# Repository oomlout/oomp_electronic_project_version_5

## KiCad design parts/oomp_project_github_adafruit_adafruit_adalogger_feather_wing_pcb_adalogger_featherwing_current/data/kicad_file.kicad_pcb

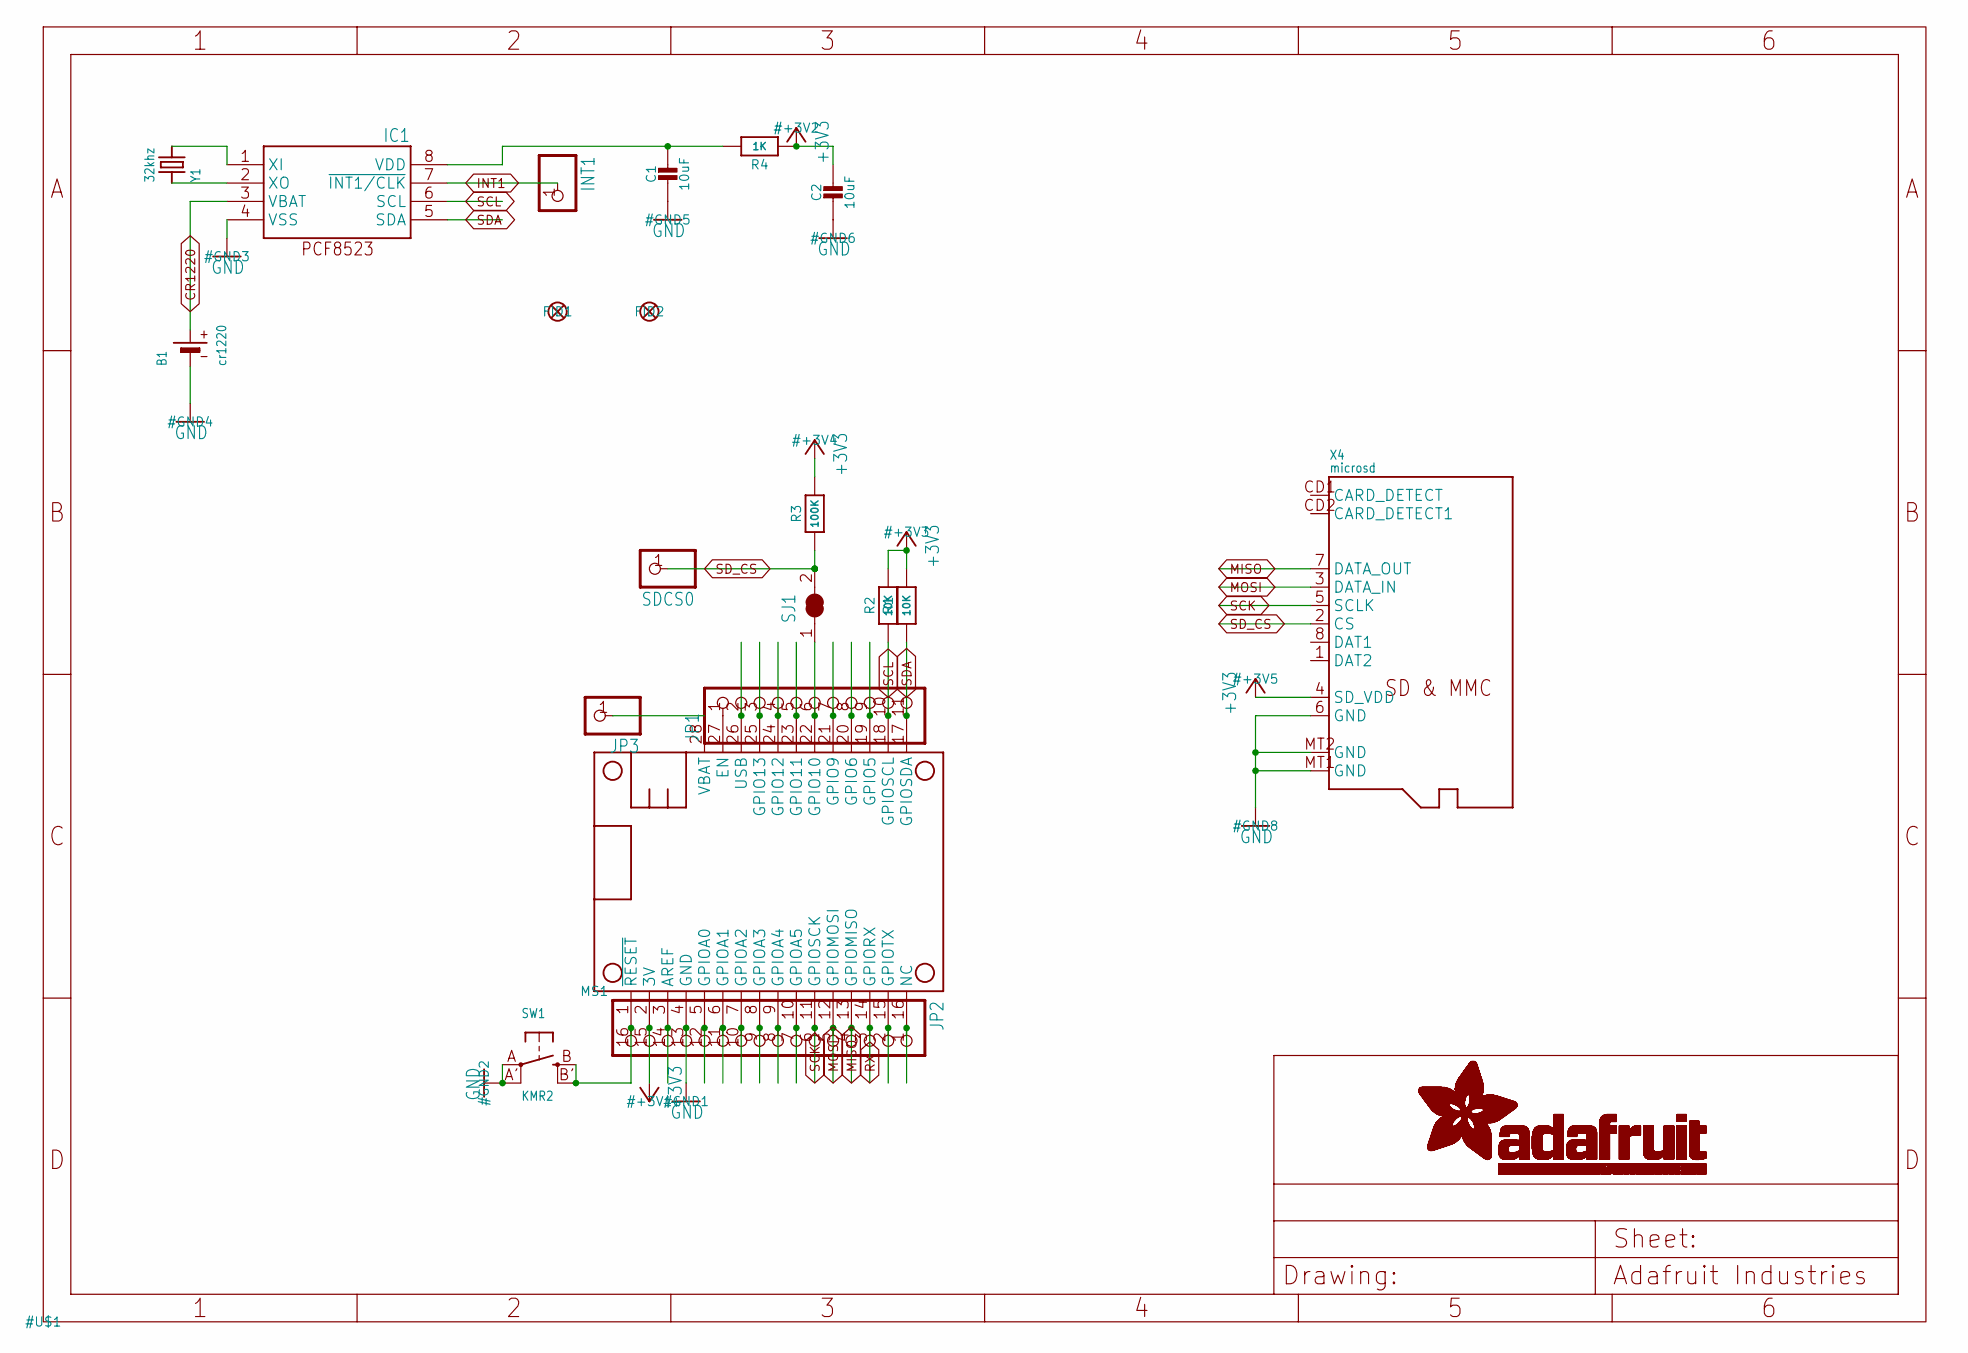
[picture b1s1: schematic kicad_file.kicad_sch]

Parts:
B1: cr1220; CR1220-2
C1, C2: 10uF; 0805-NO
FID1, FID2: FIDUCIAL_1MM
IC1: PCF8523T; SOIC8_150MIL
INT1: HEADER-1X1ROUND; 1X01_ROUND
JP1: HEADER-1X11; 1X11_ROUND
JP2: HEADER-1X16ROUND; 1X16_ROUND
JP3: HEADER-1X1ROUND; 1X01_ROUND
MS1: FEATHERWING_NODIM
R1, R2: 10K; 0603-NO
R3: 100K; 0603-NO
R4: 1K; 0603-NO
SDCS0: HEADER-1X1ROUND; 1X01_ROUND
SJ1: SOLDERJUMPER_CLOSED; SOLDERJUMPER_CLOSEDWIRE
SW1: KMR2; BTN_KMR2_4.6X2.8
X4: microsd; MICROSD
Y1: 32khz; CRYSTAL_8X3.8

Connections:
+3V3: C2.1, JP2.15, MS1.2 (3V), R1.2, R2.2, R3.2, R4.1, X4.4 (SD_VDD)
A: JP2.12, MS1.5 (GPIOA0)
AREF: JP2.14, MS1.3 (AREF)
B: JP2.11, MS1.6 (GPIOA1)
C: JP2.10, MS1.7 (GPIOA2)
CR1220: B1.+, IC1.3 (VBAT)
CS: JP1.6, MS1.22 (GPIO10), SJ1.1
D: JP2.9, MS1.8 (GPIOA3)
E: JP2.8, MS1.9 (GPIOA4)
EN: JP1.1, MS1.27 (EN)
F: JP2.7, MS1.10 (GPIOA5)
G: JP2.1, MS1.16 (NC)
GND: B1.-, C1.2, C2.2, IC1.4 (VSS), JP2.13, MS1.4 (GND), SW1.A, SW1.A' (P1), X4.6 (GND), X4.MT1 (GND), X4.MT2 (GND)
H: JP1.9, MS1.19 (GPIO5)
I: JP1.8, MS1.20 (GPIO6)
INT1: IC1.7 (~INT1/CLK), INT1.1
J: JP1.7, MS1.21 (GPIO9)
L: JP1.5, MS1.23 (GPIO11)
M: JP1.4, MS1.24 (GPIO12)
MISO: JP2.4, MS1.13 (GPIOMISO), X4.7 (DATA_OUT)
MOSI: JP2.5, MS1.12 (GPIOMOSI), X4.3 (DATA_IN)
N: JP1.3, MS1.25 (GPIO13)
unnamed: C1.1, IC1.8 (VDD), R4.2
unnamed: IC1.1 (XI), Y1.P$4 (2)
unnamed: IC1.2 (XO), Y1.P$1 (1)
RESET: JP2.16, MS1.1 (~RESET), SW1.B (S), SW1.B' (S1)
RX: JP2.3, MS1.14 (GPIORX)
SCK: JP2.6, MS1.11 (GPIOSCK), X4.5 (SCLK)
SCL: IC1.6 (SCL), JP1.10, MS1.18 (GPIOSCL), R2.1
SDA: IC1.5 (SDA), JP1.11, MS1.17 (GPIOSDA), R1.1
SD_CS: R3.1, SDCS0.1, SJ1.2, X4.2 (CS)
TX: JP2.2, MS1.15 (GPIOTX)
USB: JP1.2, MS1.26 (USB)
VBAT: JP3.1, MS1.28 (VBAT)

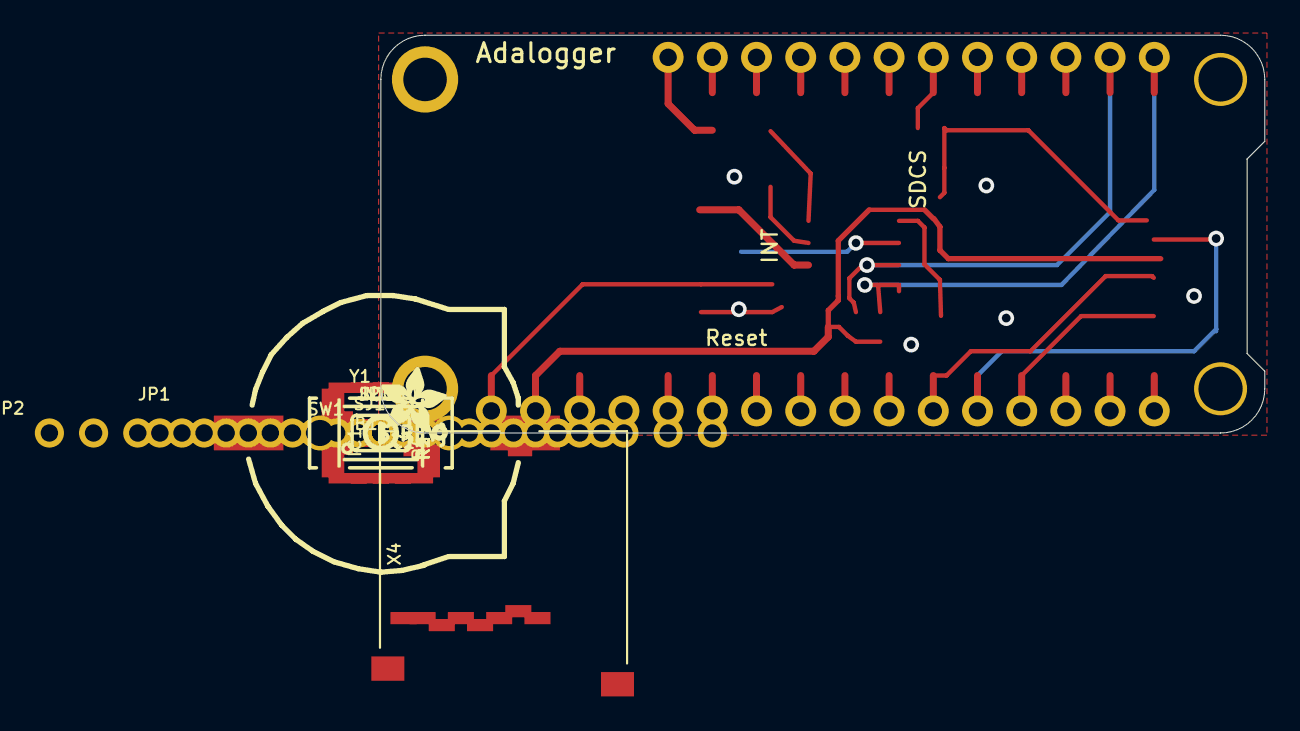
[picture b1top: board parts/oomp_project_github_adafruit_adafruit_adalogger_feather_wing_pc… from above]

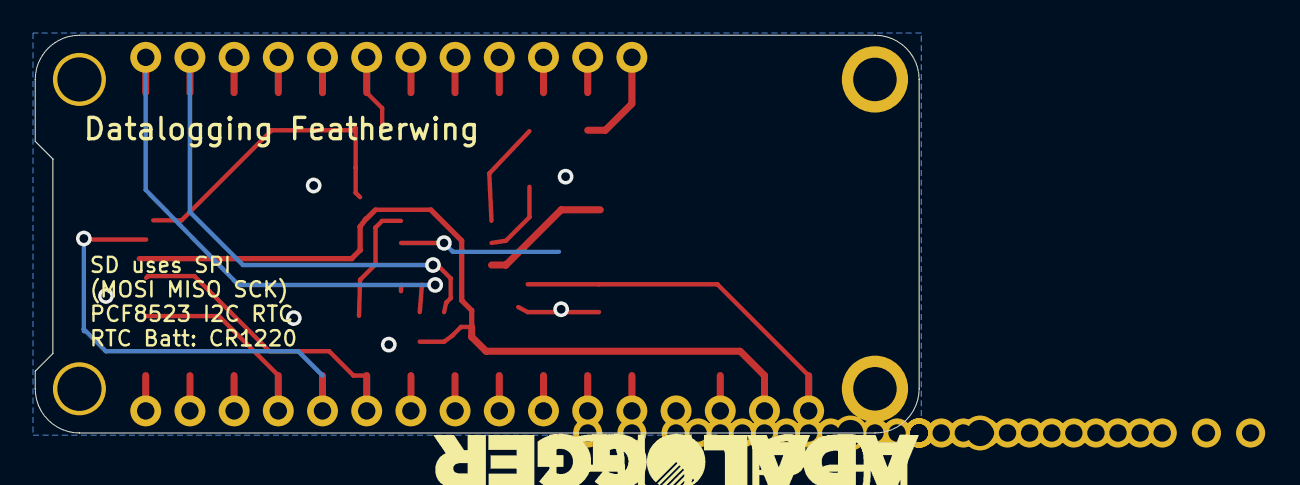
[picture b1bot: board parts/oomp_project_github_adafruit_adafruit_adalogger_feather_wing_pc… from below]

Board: 2 copper layers, 50.8 x 22.9 mm, 24 parts (2 on the bottom side), 34 nets.

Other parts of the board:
U$2: FEATHERLOGO
U$3: ADALOGGER_LOGO
U$4: ADAFRUIT_3.5MM
U$5: PCBFEAT-REV-040

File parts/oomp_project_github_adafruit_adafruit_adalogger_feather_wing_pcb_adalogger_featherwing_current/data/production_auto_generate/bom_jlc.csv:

Comment,Designator,Footprint,LCSC Part #
,"INT1,JP3,SDCS0",adalogger featherwing-import-fps:1X01_ROUND,C7501259
,JP1,adalogger featherwing-import-fps:1X11_ROUND,C2894934
,JP2,adalogger featherwing-import-fps:1X16_ROUND,C7501270
,U$4,adalogger featherwing-import-fps:ADAFRUIT_3.5MM,
,U$3,adalogger featherwing-import-fps:ADALOGGER_LOGO,
,U$2,adalogger featherwing-import-fps:FEATHERLOGO,
,U$5,adalogger featherwing-import-fps:PCBFEAT-REV-040,
100K,R3,adalogger featherwing-import-fps:0603-NO,C25803
10K,"R1,R2",adalogger featherwing-import-fps:0603-NO,C98220
10uF,"C1,C2",adalogger featherwing-import-fps:0805-NO,
1K,R4,adalogger featherwing-import-fps:0603-NO,C2907002
32khz,Y1,adalogger featherwing-import-fps:CRYSTAL_8X3.8,
cr1220,B1,adalogger featherwing-import-fps:CR1220-2,
FEATHERWING_NODIM,MS1,adalogger featherwing-import-fps:FEATHERWING_NODIM,
KMR2,SW1,adalogger featherwing-import-fps:BTN_KMR2_4.6X2.8,
microsd,X4,adalogger featherwing-import-fps:MICROSD,
PCF8523T,IC1,adalogger featherwing-import-fps:SOIC8_150MIL,

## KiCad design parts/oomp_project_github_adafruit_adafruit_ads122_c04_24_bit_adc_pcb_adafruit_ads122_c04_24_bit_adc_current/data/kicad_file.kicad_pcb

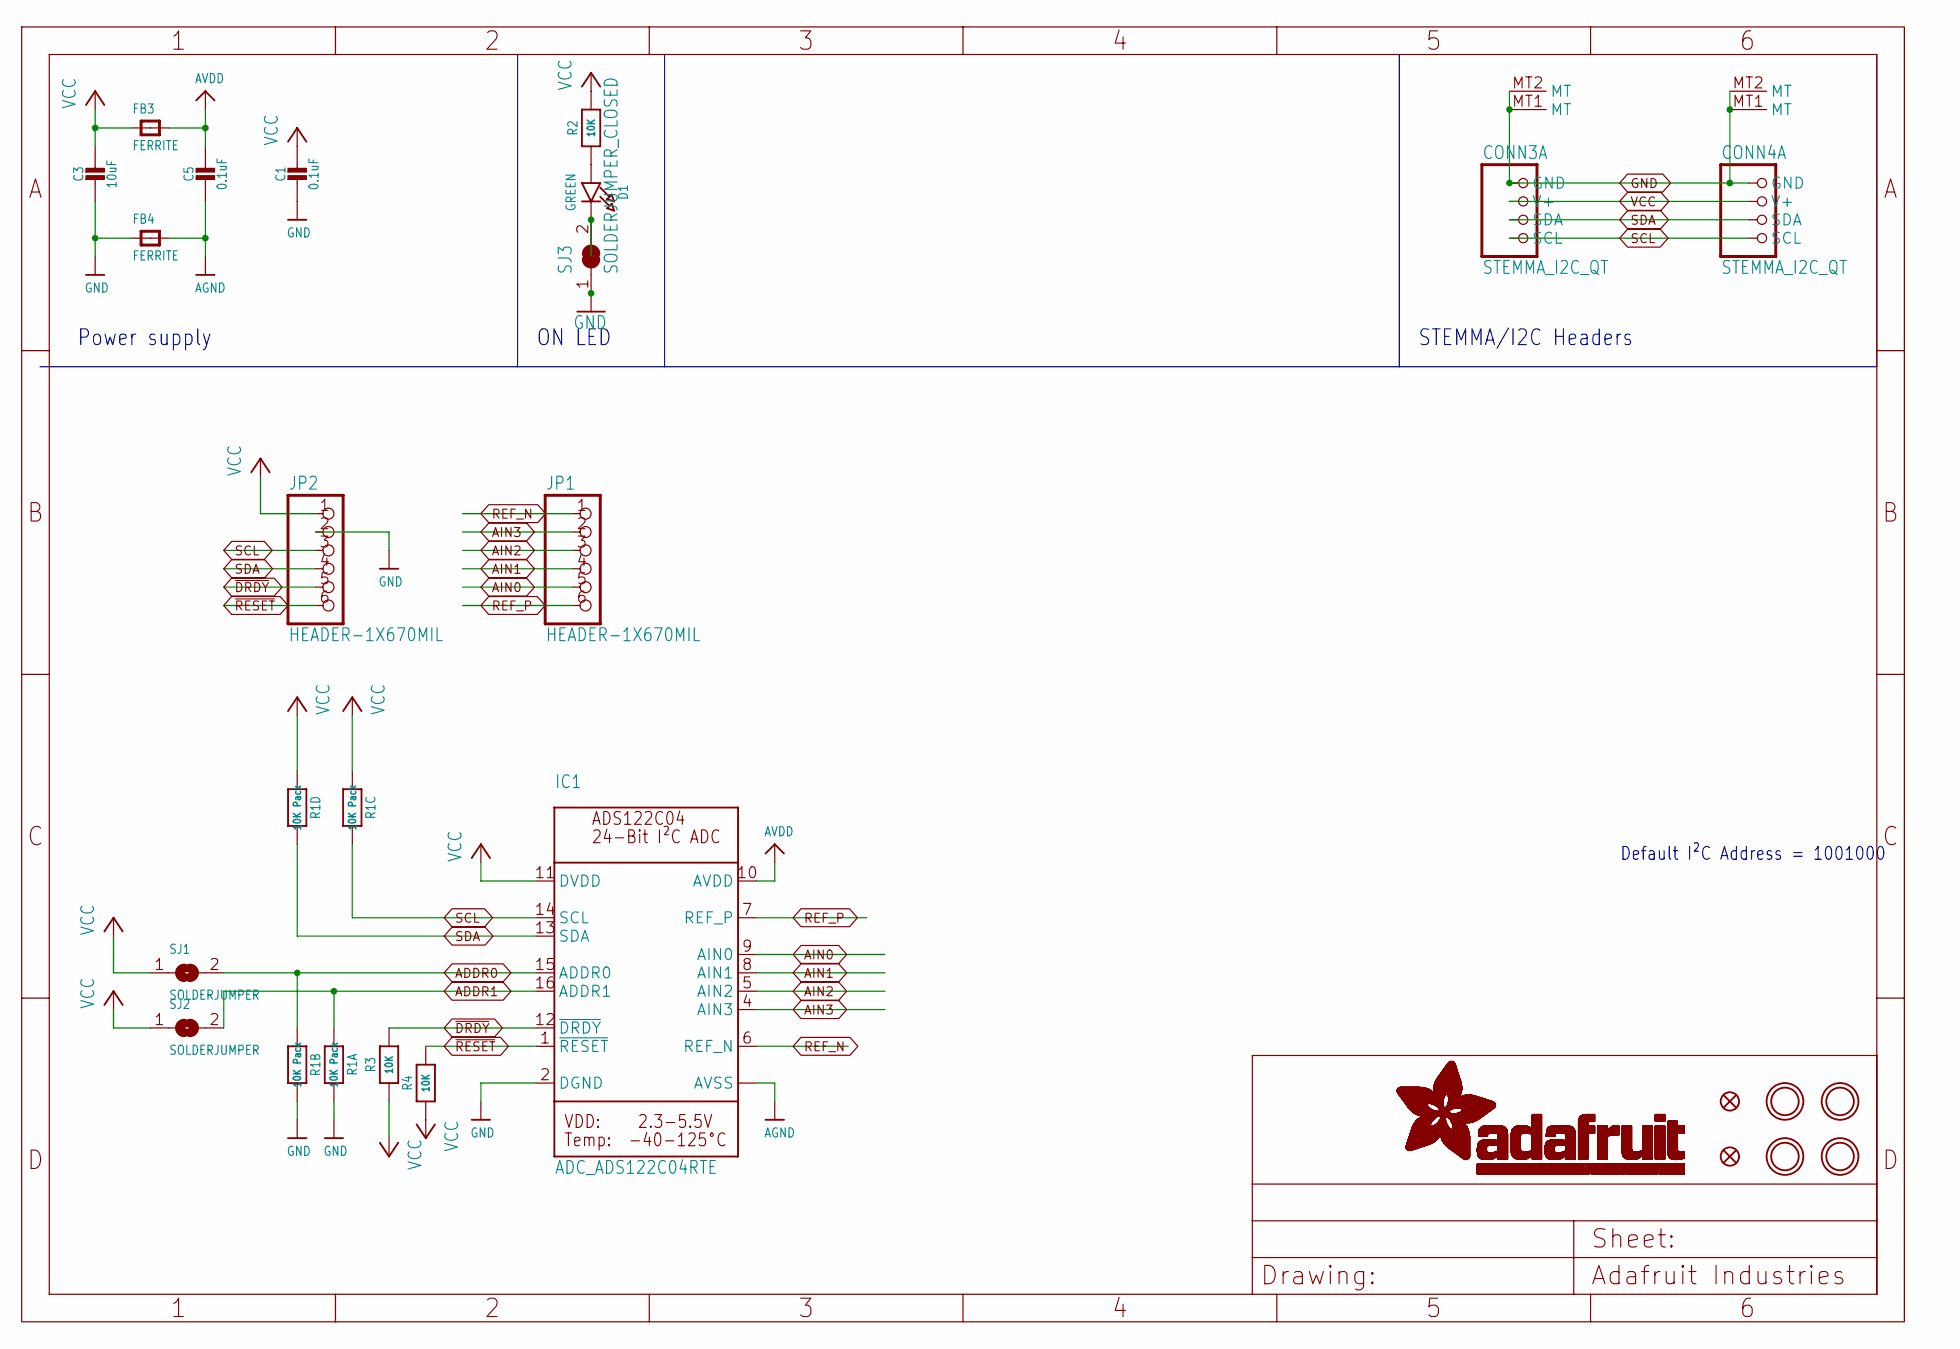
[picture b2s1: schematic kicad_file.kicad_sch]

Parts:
C1, C5: 0.1uF; 0603-NO
C3: 10uF; 0805-NO
CONN3, CONN4: STEMMA_I2C_QT; JST_SH4; LCSC C2845363
D1: GREEN; CHIPLED_0603_NOOUTLINE
FB3, FB4: FERRITE; 0603-NO
FID3, FID4: FIDUCIAL_0.5MM
IC1: ADC_ADS122C04RTE; WQFN16
JP1, JP2: HEADER-1X670MIL; 1X06_ROUND_70
R1: 10K Pack; RESPACK_4X0603
R2, R3, R4: 10K; 0603-NO
SJ1, SJ2: SOLDERJUMPER; SOLDERJUMPER_ARROW_NOPASTE
SJ3: SOLDERJUMPER_CLOSED; SOLDERJUMPER_CLOSEDWIRE
U$25, U$27, U$29, U$30: MOUNTINGHOLE2.5; MOUNTINGHOLE_2.5_PLATED

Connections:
ADDR0: IC1.15 (ADDR0), R1.2 (1), SJ1.2
ADDR1: IC1.16 (ADDR1), R1.1, SJ2.2
AGND: C5.2, FB4.2, IC1.3 (AVSS), IC1.THERM (AVSS)
AIN0: IC1.9 (AIN0), JP1.5
AIN1: IC1.8 (AIN1), JP1.4
AIN2: IC1.5 (AIN2), JP1.3
AIN3: IC1.4 (AIN3), JP1.2
AVDD: C5.1, FB3.2, IC1.10 (AVDD)
GND: C1.2, C3.2, CONN3.1 (GND), CONN3.MT1 (MT), CONN3.MT2 (MT), CONN4.1 (GND), CONN4.MT1 (MT), CONN4.MT2 (MT), FB4.1, IC1.2 (DGND), JP2.2, R1.7 (2), R1.8 (2), SJ3.1
unnamed: D1.C, SJ3.2
unnamed: D1.A, R2.1
REF_N: IC1.6 (REF_N), JP1.1
REF_P: IC1.7 (REF_P), JP1.6
SCL: CONN3.4 (SCL), CONN4.4 (SCL), IC1.14 (SCL), JP2.3, R1.3 (1)
SDA: CONN3.3 (SDA), CONN4.3 (SDA), IC1.13 (SDA), JP2.4, R1.4 (1)
VCC: C1.1, C3.1, CONN3.2 (V+), CONN4.2 (V+), FB3.1, IC1.11 (DVDD), JP2.1, R1.5 (2), R1.6 (2), R2.2, R3.1, R4.1, SJ1.1, SJ2.1
~DRDY: IC1.12 (~DRDY), JP2.5, R3.2
~RESET: IC1.1 (~RESET), JP2.6, R4.2

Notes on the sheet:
Default I²C Address = 1001000
Power supply
STEMMA/I2C Headers
ON LED

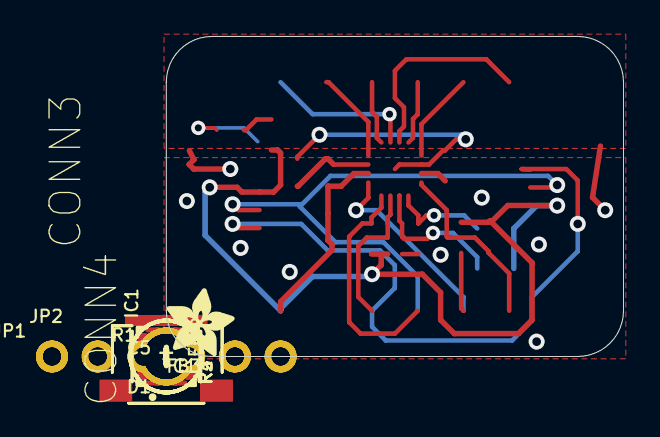
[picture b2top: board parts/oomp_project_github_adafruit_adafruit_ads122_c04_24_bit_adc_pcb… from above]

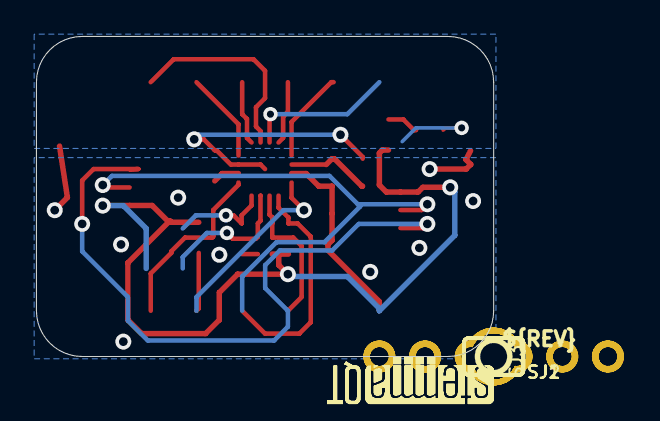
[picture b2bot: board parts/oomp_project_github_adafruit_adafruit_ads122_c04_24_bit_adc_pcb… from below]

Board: 2 copper layers, 25.4 x 17.8 mm, 48 parts (12 on the bottom side), 18 nets.

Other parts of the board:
PLABEL0: PLABEL0
PLABEL1: PLABEL1
PLABEL2: PLABEL2
PLABEL3: PLABEL3
PLABEL4: PLABEL4
PLABEL5: PLABEL5
PLABEL6: PLABEL6
PLABEL7: PLABEL7
PLABEL8: PLABEL8
PLABEL9: PLABEL9
PLABEL10: PLABEL10
PLABEL11: PLABEL11
PLABEL12: PLABEL12
PLABEL13: PLABEL13
PLABEL14: PLABEL14
PLABEL15: PLABEL15
PLABEL16: PLABEL16
PLABEL17: PLABEL17
PLABEL18: PLABEL18
PLABEL19: PLABEL19
U$32: ADAFRUIT_3.5MM
U$33: PCBFEAT-REV-040
U$34, U$35: STEMMAQT

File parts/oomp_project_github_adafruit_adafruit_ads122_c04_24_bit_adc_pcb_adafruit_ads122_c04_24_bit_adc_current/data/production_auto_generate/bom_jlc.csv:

Comment,Designator,Footprint,LCSC Part #
,"JP1,JP2",Adafruit ADS122C04 24-Bit ADC-import-fps:1X06_ROUND_70,C37208
,U$32,Adafruit ADS122C04 24-Bit ADC-import-fps:ADAFRUIT_3.5MM,
,U$33,Adafruit ADS122C04 24-Bit ADC-import-fps:PCBFEAT-REV-040,
,PLABEL0,Adafruit ADS122C04 24-Bit ADC-import-fps:PLABEL0,
,PLABEL1,Adafruit ADS122C04 24-Bit ADC-import-fps:PLABEL1,
,PLABEL10,Adafruit ADS122C04 24-Bit ADC-import-fps:PLABEL10,
,PLABEL11,Adafruit ADS122C04 24-Bit ADC-import-fps:PLABEL11,
,PLABEL12,Adafruit ADS122C04 24-Bit ADC-import-fps:PLABEL12,
,PLABEL13,Adafruit ADS122C04 24-Bit ADC-import-fps:PLABEL13,
,PLABEL14,Adafruit ADS122C04 24-Bit ADC-import-fps:PLABEL14,
,PLABEL15,Adafruit ADS122C04 24-Bit ADC-import-fps:PLABEL15,
,PLABEL16,Adafruit ADS122C04 24-Bit ADC-import-fps:PLABEL16,
,PLABEL17,Adafruit ADS122C04 24-Bit ADC-import-fps:PLABEL17,
,PLABEL18,Adafruit ADS122C04 24-Bit ADC-import-fps:PLABEL18,
,PLABEL19,Adafruit ADS122C04 24-Bit ADC-import-fps:PLABEL19,
,PLABEL2,Adafruit ADS122C04 24-Bit ADC-import-fps:PLABEL2,
,PLABEL3,Adafruit ADS122C04 24-Bit ADC-import-fps:PLABEL3,
,PLABEL4,Adafruit ADS122C04 24-Bit ADC-import-fps:PLABEL4,
,PLABEL5,Adafruit ADS122C04 24-Bit ADC-import-fps:PLABEL5,
,PLABEL6,Adafruit ADS122C04 24-Bit ADC-import-fps:PLABEL6,
,PLABEL7,Adafruit ADS122C04 24-Bit ADC-import-fps:PLABEL7,
,PLABEL8,Adafruit ADS122C04 24-Bit ADC-import-fps:PLABEL8,
,PLABEL9,Adafruit ADS122C04 24-Bit ADC-import-fps:PLABEL9,
,"U$34,U$35",Adafruit ADS122C04 24-Bit ADC-import-fps:STEMMAQT,
0.1uF,"C1,C5",Adafruit ADS122C04 24-Bit ADC-import-fps:0603-NO,C14663
10K,"R2,R3,R4",Adafruit ADS122C04 24-Bit ADC-import-fps:0603-NO,C98220
10K Pack,R1,Adafruit ADS122C04 24-Bit ADC-import-fps:RESPACK_4X0603,C98220
10uF,C3,Adafruit ADS122C04 24-Bit ADC-import-fps:0805-NO,
ADC_ADS122C04RTE,IC1,Adafruit ADS122C04 24-Bit ADC-import-fps:WQFN16,
FERRITE,"FB3,FB4",Adafruit ADS122C04 24-Bit ADC-import-fps:0603-NO,
GREEN,D1,Adafruit ADS122C04 24-Bit ADC-import-fps:CHIPLED_0603_NOOUTLINE,
STEMMA_I2C_QT,"CONN3,CONN4",Adafruit ADS122C04 24-Bit ADC-import-fps:JST_SH4,C160404

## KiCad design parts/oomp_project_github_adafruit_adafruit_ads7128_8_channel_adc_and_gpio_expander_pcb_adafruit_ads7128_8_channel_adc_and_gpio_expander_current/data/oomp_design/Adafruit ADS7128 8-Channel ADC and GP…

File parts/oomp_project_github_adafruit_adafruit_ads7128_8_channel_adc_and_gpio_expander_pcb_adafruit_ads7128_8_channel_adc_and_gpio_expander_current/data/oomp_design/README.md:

# OOMP KiCad design copy

Open `Adafruit ADS7128 8-Channel ADC and GPIO Expander.kicad_pro` (or the `.kicad_pcb` / `.kicad_sch`) in KiCad. Local OOMP libraries are under `libraries/`. Original inputs are preserved in [../original/](../original/).

Only verified unchanged installed KiCad defaults were renamed. Modified, custom, unmatched and unavailable items remain unchanged. Soldering variants are never swapped during conversion. Existing pad coordinates, nets and UUIDs are preserved.

See [conversion_report.yaml](conversion_report.yaml) for every conversion and skip. Copy this directory before editing; regeneration refuses to overwrite edited design files.

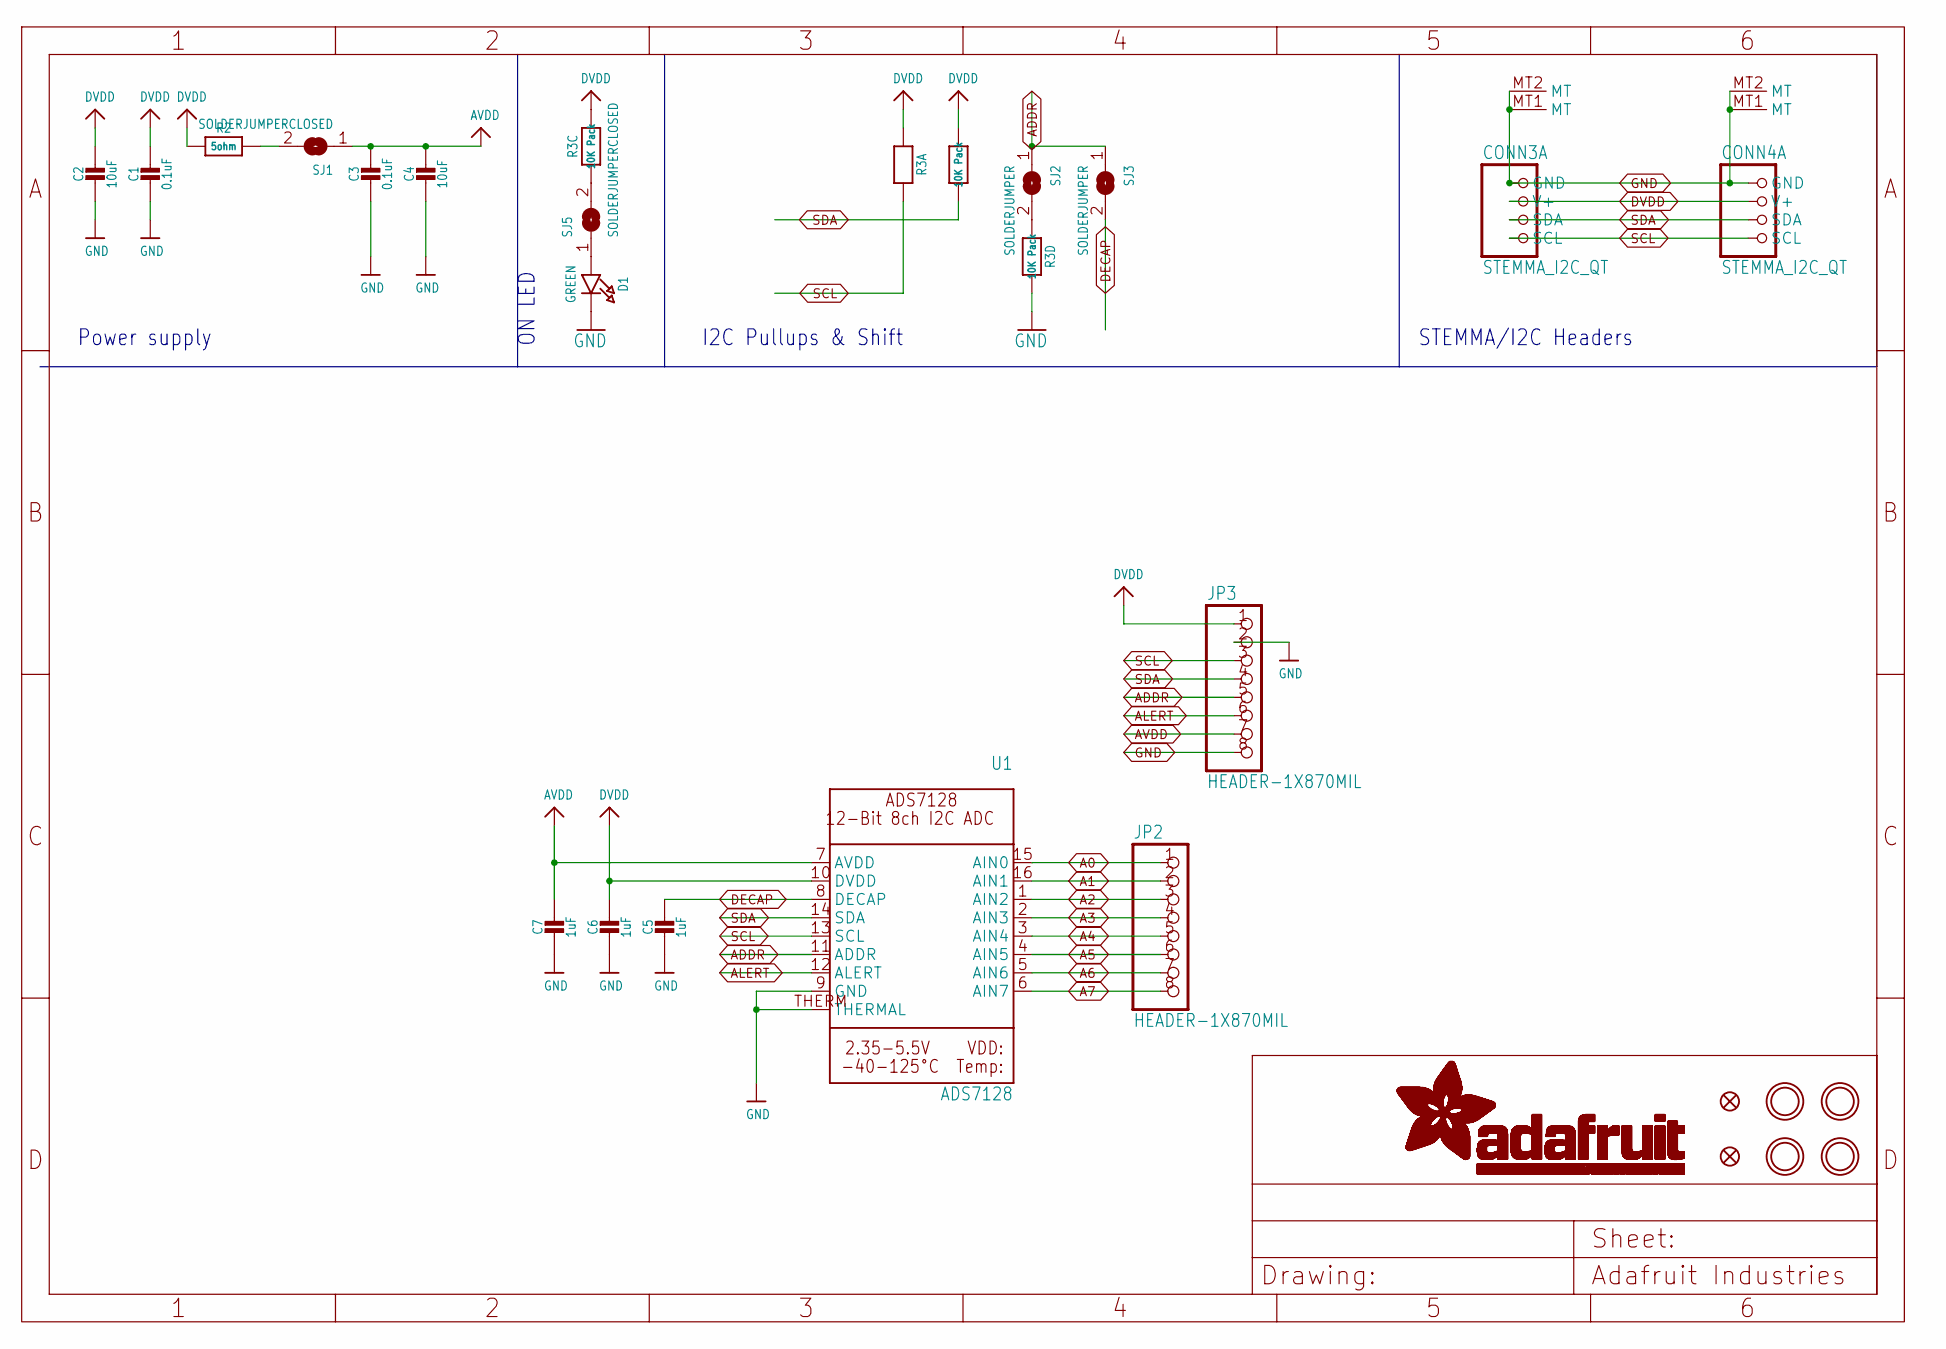
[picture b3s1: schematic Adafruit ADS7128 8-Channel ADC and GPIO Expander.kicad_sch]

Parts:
C1, C3: 0.1uF; 0603-NO
C2, C4: 10uF; 0805-NO
C5, C6, C7: 1uF; 0603-NO
CONN3, CONN4: STEMMA_I2C_QT; JST_SH4; LCSC C2905006
D1: GREEN; CHIPLED_0603_NOOUTLINE
FID3, FID4: FIDUCIAL_0.5MM
JP2, JP3: HEADER-1X870MIL; 1X08_ROUND_70
R2: 5ohm; 0603-NO
R3: 10K Pack; RESPACK_4X0603
SJ1, SJ5: SOLDERJUMPERCLOSED; SOLDERJUMPER_CLOSEDWIRE
SJ2, SJ3: SOLDERJUMPER; SOLDERJUMPER_ARROW_NOPASTE
U1: ADS7128; WQFN16
U$1, U$17, U$19, U$21: MOUNTINGHOLE2.5; MOUNTINGHOLE_2.5_PLATED

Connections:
A0: JP2.1, U1.15 (AIN0)
A1: JP2.2, U1.16 (AIN1)
A2: JP2.3, U1.1 (AIN2)
A3: JP2.4, U1.2 (AIN3)
A4: JP2.5, U1.3 (AIN4)
A5: JP2.6, U1.4 (AIN5)
A6: JP2.7, U1.5 (AIN6)
A7: JP2.8, U1.6 (AIN7)
ADDR: JP3.5, SJ2.1, SJ3.1, U1.11 (ADDR)
ALERT: JP3.6, U1.12 (ALERT)
AVDD: C3.1, C4.1, C7.1, JP3.7, SJ1.1, U1.7 (AVDD)
DECAP: C5.1, SJ3.2, U1.8 (DECAP)
DVDD: C1.1, C2.1, C6.1, CONN3.2 (V+), CONN4.2 (V+), JP3.1, R2.1, R3.1, R3.2 (1), R3.6 (2), U1.10 (DVDD)
GND: C1.2, C2.2, C3.2, C4.2, C5.2, C6.2, C7.2, CONN3.1 (GND), CONN3.MT1 (MT), CONN3.MT2 (MT), CONN4.1 (GND), CONN4.MT1 (MT), CONN4.MT2 (MT), D1.C, JP3.2, JP3.8, R3.5 (2), U1.9 (GND), U1.THERM (THERMAL)
unnamed: D1.A, SJ5.1
unnamed: R3.3 (1), SJ5.2
unnamed: R2.2, SJ1.2
unnamed: R3.4 (1), SJ2.2
SCL: CONN3.4 (SCL), CONN4.4 (SCL), JP3.3, R3.8 (2), U1.13 (SCL)
SDA: CONN3.3 (SDA), CONN4.3 (SDA), JP3.4, R3.7 (2), U1.14 (SDA)

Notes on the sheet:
ON LED
I2C Pullups & Shift
STEMMA/I2C Headers
Power supply

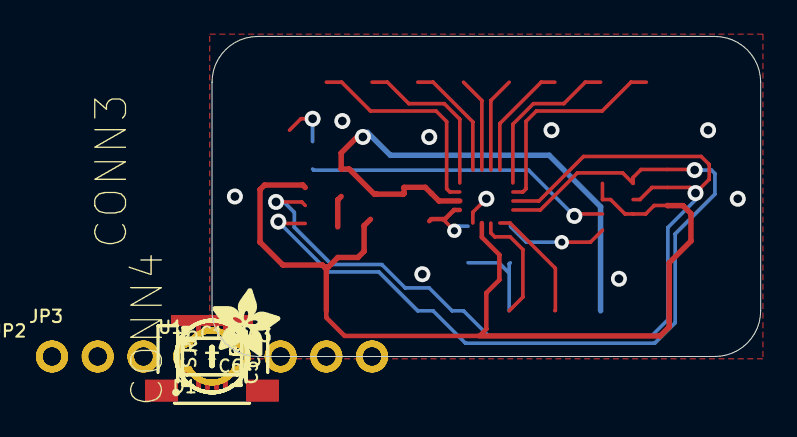
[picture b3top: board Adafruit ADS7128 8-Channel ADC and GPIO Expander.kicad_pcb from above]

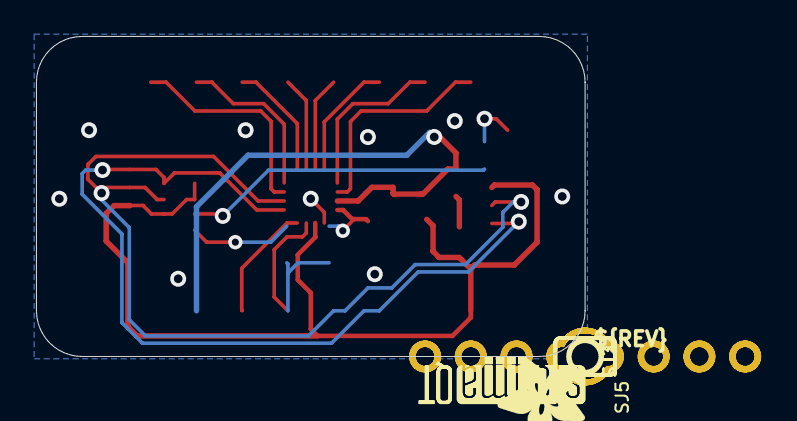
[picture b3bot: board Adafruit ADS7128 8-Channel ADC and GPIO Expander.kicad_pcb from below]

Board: 2 copper layers, 30.5 x 17.8 mm, 58 parts (14 on the bottom side), 20 nets.

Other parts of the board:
PLABEL0: PLABEL0
PLABEL2: PLABEL2
PLABEL3: PLABEL3
PLABEL4: PLABEL4
PLABEL7: PLABEL7
PLABEL10: PLABEL10
PLABEL11: PLABEL11
PLABEL12: PLABEL12
PLABEL13: PLABEL13
PLABEL14: PLABEL14
PLABEL15: PLABEL15
PLABEL16: PLABEL16
PLABEL17: PLABEL17
PLABEL20: PLABEL20
PLABEL25: PLABEL25
PLABEL26: PLABEL26
PLABEL27: PLABEL27
PLABEL28: PLABEL28
PLABEL29: PLABEL29
PLABEL30: PLABEL30
PLABEL31: PLABEL31
PLABEL32: PLABEL32
PLABEL33: PLABEL33
PLABEL34: PLABEL34
PLABEL35: PLABEL35
PLABEL36: PLABEL36
PLABEL37: PLABEL37
PLABEL38: PLABEL38
U$22: ADAFRUIT_3.5MM
U$25: PCBFEAT-REV-040
U$27: ADAFRUIT_5MM
U$30, U$31: STEMMAQT

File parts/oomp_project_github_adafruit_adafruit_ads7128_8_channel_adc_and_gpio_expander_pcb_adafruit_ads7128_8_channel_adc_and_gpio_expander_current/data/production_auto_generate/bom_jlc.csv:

Comment,Designator,Footprint,LCSC Part #
,"JP2,JP3",1X08_ROUND_70,C492421
,U$22,ADAFRUIT_3.5MM,
,U$27,ADAFRUIT_5MM,
,U$25,PCBFEAT-REV-040,
,PLABEL0,PLABEL0,
,PLABEL10,PLABEL10,
,PLABEL11,PLABEL11,
,PLABEL12,PLABEL12,
,PLABEL13,PLABEL13,
,PLABEL14,PLABEL14,
,PLABEL15,PLABEL15,
,PLABEL16,PLABEL16,
,PLABEL17,PLABEL17,
,PLABEL2,PLABEL2,
,PLABEL20,PLABEL20,
,PLABEL25,PLABEL25,
,PLABEL26,PLABEL26,
,PLABEL27,PLABEL27,
,PLABEL28,PLABEL28,
,PLABEL29,PLABEL29,
,PLABEL3,PLABEL3,
,PLABEL30,PLABEL30,
,PLABEL31,PLABEL31,
,PLABEL32,PLABEL32,
,PLABEL33,PLABEL33,
,PLABEL34,PLABEL34,
,PLABEL35,PLABEL35,
,PLABEL36,PLABEL36,
,PLABEL37,PLABEL37,
,PLABEL38,PLABEL38,
,PLABEL4,PLABEL4,
,PLABEL7,PLABEL7,
,"U$30,U$31",STEMMAQT,
0.1uF,"C1,C3",0603-NO,C14663
10K Pack,R3,RESPACK_4X0603,C98220
10uF,"C2,C4",0805-NO,
1uF,"C5,C6,C7",0603-NO,C5673
5ohm,R2,0603-NO,
ADS7128,U1,WQFN16,
GREEN,D1,CHIPLED_0603_NOOUTLINE,
STEMMA_I2C_QT,"CONN3,CONN4",JST_SH4,C160404

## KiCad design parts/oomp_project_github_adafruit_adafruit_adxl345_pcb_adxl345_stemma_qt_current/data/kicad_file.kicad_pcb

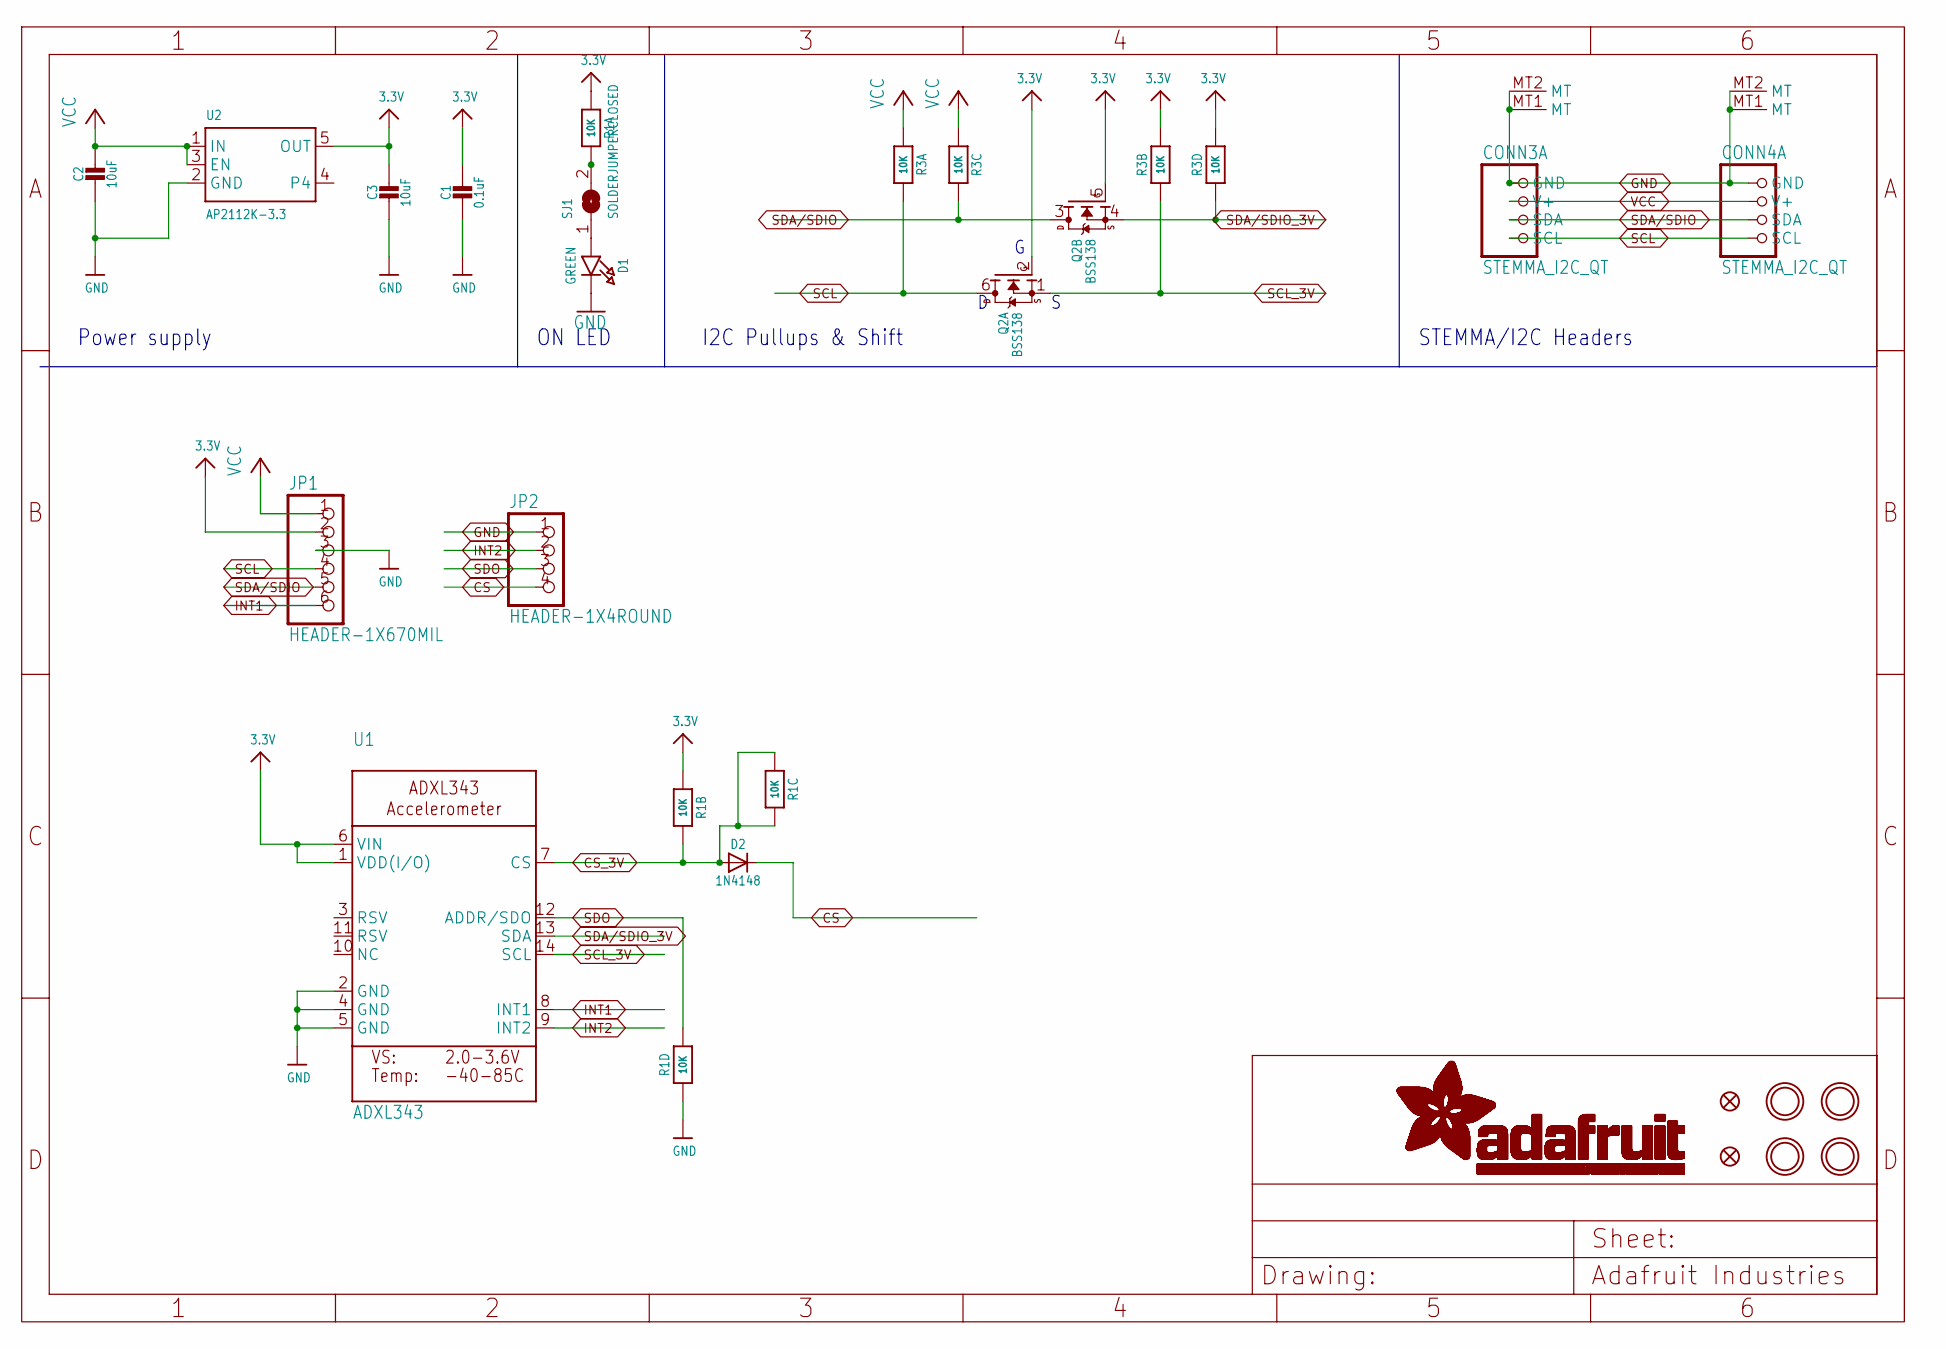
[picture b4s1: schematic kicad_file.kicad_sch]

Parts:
C1: 0.1uF; 0603-NO
C2: 10uF; _0805MP
C3: 10uF; 0805-NO
CONN3, CONN4: STEMMA_I2C_QT; JST_SH4
D1: GREEN; CHIPLED_0603_NOOUTLINE
D2: 1N4148; SOD-323
FID3, FID4: FIDUCIAL_1MM
JP1: HEADER-1X670MIL; 1X06_ROUND_70
JP2: HEADER-1X4ROUND; 1X04_ROUND
Q2: BSS138; SOT363
R1, R3: 10K; RESPACK_4X0603
SJ1: SOLDERJUMPERCLOSED; SOLDERJUMPER_CLOSEDWIRE
U1: ADXL343; LGA14
U2: AP2112K-3.3; SOT23-5
U$1, U$17, U$19, U$21: MOUNTINGHOLE2.5; MOUNTINGHOLE_2.5_PLATED

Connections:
3.3V: C1.1, C3.1, JP1.2, Q2.2 (G), Q2.5 (G), R1.1, R1.2 (1), R3.2 (1), R3.4 (1), U1.1 (VDD(I/O)), U1.6 (VIN), U2.5 (OUT)
CS: D2.C, JP2.4
CS_3V: D2.A, R1.3 (1), R1.6 (2), R1.7 (2), U1.7 (CS)
GND: C1.2, C2.2, C3.2, CONN3.1 (GND), CONN3.MT1 (MT), CONN3.MT2 (MT), CONN4.1 (GND), CONN4.MT1 (MT), CONN4.MT2 (MT), D1.C, JP1.3, JP2.1, R1.4 (1), U1.2 (GND), U1.4 (GND), U1.5 (GND), U2.2 (GND)
INT1: JP1.6, U1.8 (INT1)
INT2: JP2.2, U1.9 (INT2)
unnamed: R1.8 (2), SJ1.2
unnamed: D1.A, SJ1.1
SCL: CONN3.4 (SCL), CONN4.4 (SCL), JP1.4, Q2.6 (D), R3.8 (2)
SCL_3V: Q2.1 (S), R3.7 (2), U1.14 (SCL)
SDA/SDIO: CONN3.3 (SDA), CONN4.3 (SDA), JP1.5, Q2.3 (D), R3.6 (2)
SDA/SDIO_3V: Q2.4 (S), R3.5 (2), U1.13 (SDA)
SDO: JP2.3, R1.5 (2), U1.12 (ADDR/SDO)
VCC: C2.1, CONN3.2 (V+), CONN4.2 (V+), JP1.1, R3.1, R3.3 (1), U2.1 (IN), U2.3 (EN)

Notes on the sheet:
Power supply
I2C Pullups & Shift
ON LED
STEMMA/I2C Headers

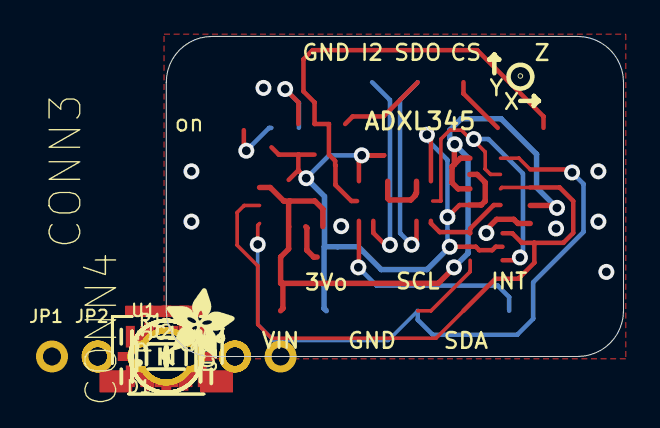
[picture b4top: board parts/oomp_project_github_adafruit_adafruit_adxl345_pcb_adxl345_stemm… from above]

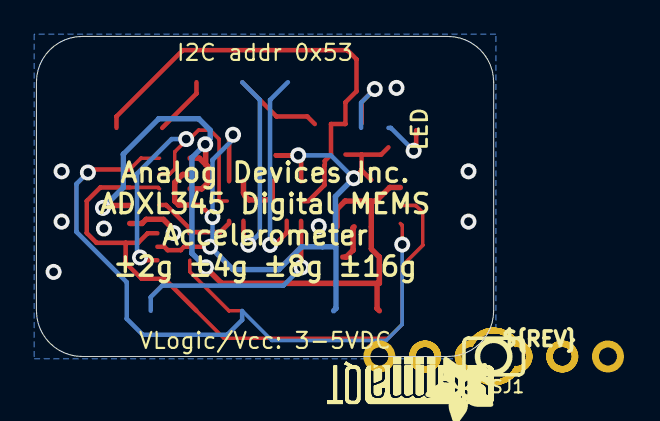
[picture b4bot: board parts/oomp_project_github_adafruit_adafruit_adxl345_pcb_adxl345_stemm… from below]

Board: 2 copper layers, 25.4 x 17.8 mm, 26 parts (5 on the bottom side), 14 nets.

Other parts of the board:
U$4, U$11: ADAFRUIT_3.5MM
U$25: PCBFEAT-REV-040
U$30, U$31: STEMMAQT

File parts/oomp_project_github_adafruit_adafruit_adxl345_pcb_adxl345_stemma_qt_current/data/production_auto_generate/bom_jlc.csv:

Comment,Designator,Footprint,LCSC Part #
,JP2,ADXL345 STEMMA QT-import-fps:1X04_ROUND,C42431795
,JP1,ADXL345 STEMMA QT-import-fps:1X06_ROUND_70,C37208
,"U$4,U$11",ADXL345 STEMMA QT-import-fps:ADAFRUIT_3.5MM,
,U$25,ADXL345 STEMMA QT-import-fps:PCBFEAT-REV-040,
,"U$30,U$31",ADXL345 STEMMA QT-import-fps:STEMMAQT,
0.1uF,C1,ADXL345 STEMMA QT-import-fps:0603-NO,C14663
10K,"R1,R3",ADXL345 STEMMA QT-import-fps:RESPACK_4X0603,C98220
10uF,C3,ADXL345 STEMMA QT-import-fps:0805-NO,
10uF,C2,ADXL345 STEMMA QT-import-fps:_0805MP,
1N4148,D2,ADXL345 STEMMA QT-import-fps:SOD-323,
ADXL343,U1,ADXL345 STEMMA QT-import-fps:LGA14,
AP2112K-3.3,U2,ADXL345 STEMMA QT-import-fps:SOT23-5,
BSS138,Q2,ADXL345 STEMMA QT-import-fps:SOT363,
GREEN,D1,ADXL345 STEMMA QT-import-fps:CHIPLED_0603_NOOUTLINE,
STEMMA_I2C_QT,"CONN3,CONN4",ADXL345 STEMMA QT-import-fps:JST_SH4,C160404

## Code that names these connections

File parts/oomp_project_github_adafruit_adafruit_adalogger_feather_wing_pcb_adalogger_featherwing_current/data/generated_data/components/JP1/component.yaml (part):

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      connected_to:
      - reference: MS1
        pin_number: '25'
        pin_name: GPIO13
    - number: '4'
      name: '4'
      electrical_type: passive
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      connected_to:
      - reference: MS1
        pin_number: '24'
        pin_name: GPIO12
    - number: '5'
      name: '5'
      electrical_type: passive
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      connected_to:
      - reference: MS1
        pin_number: '23'
        pin_name: GPIO11
    - number: '6'
      name: '6'
      electrical_type: passive
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      connected_to:
      - reference: MS1
        pin_number: '22'
        pin_name: GPIO10
      - reference: SJ1
        pin_number: '1'
        pin_name: '1'
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      connected_to:
      - reference: MS1
        pin_number: '21'
        pin_name: GPIO9
    - number: '8'
      name: '8'
      electrical_type: passive
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      connected_to:
      - reference: MS1
        pin_number: '20'
        pin_name: GPIO6
    - number: '9'
      name: '9'
      electrical_type: passive
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      connected_to:
      - reference: MS1
        pin_number: '19'
        pin_name: GPIO5
    - number: '10'
      name: '10'
      electrical_type: passive
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    pin_name: GPIOSCL
  - reference: MS1
    pin_number: '19'
    pin_name: GPIO5
  - reference: MS1
    pin_number: '20'
    pin_name: GPIO6
  - reference: MS1
    pin_number: '21'
    pin_name: GPIO9
  - reference: MS1
    pin_number: '22'
    pin_name: GPIO10
  - reference: MS1
    pin_number: '23'
    pin_name: GPIO11
  - reference: MS1
    pin_number: '24'
    pin_name: GPIO12
  - reference: MS1
    pin_number: '25'
    pin_name: GPIO13
  - reference: MS1
    pin_number: '26'
    pin_name: USB
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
